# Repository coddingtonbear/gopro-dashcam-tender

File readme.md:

I use my GoPro as a dashcam, and although I rarely need to take any footage
off of my device, the GoPro will slowly accumulate videos over time.  This
device provides an easy way for me to clear the GoPro at the end of the 
day by just plugging my GoPro into it as its charger.

## Components Required

In order of decreasing expense:

* 1x ESP-12F: These can be obtained for roughly $2 on AliExpress.  Other similar packages of the ESP8266 wifi module, or _maybe_ even the ESP-01 module should work with minimal modifications to the layout and schematic.
* 1x CH340G: ~$0.50 on AliExpress.
* 1x SOT-223 3.3V Voltage Regulator
* 2x SOT-23 NPN Transistors for the UART->ESP8266 reset circuit.  Note that there are alternative reset circuits.  See below for details.
* 1x HC-49 12MHz crystal
* Miscellaneous passives.

See the schematic's netlist for more details.

## Procedure

Essentially, what this device does is:

* Wait for a GoPro to be plugged-in to the USB-A port.  This can be detected because of the way connected USB devices pull up the D+/D- lines to indicate their operating speed.
* Connect to my home WIFI network to get an up-to-date UTC time using NTP.  Immediately disconnecting from my home WIFI network.
* Connect to the GoPro WIFI network, then:
  * Set the GoPro's time.
  * Clear all stored media.
  * Turn off the GoPro.

## Schematic

## Errata

You'll notice two differences between the above schematic and the photo of the board above:

* I had originally intended to control the power supply to the attached GoPro using a mosfet (you'll see a jumper lead in the above photo between two of three leads nearby the USB-A connector.  It should've been clearer earlier, but I won't be able to detect the GoPro being plugged-in unless I'm supplying 5V; because the GoPro won't pull on the D+/D- lines until it is being supplied with voltage.
* I never populated the RGB LED in the bottom-left area of the board.  The footprint I've used in the above photo is essentially impossible to use on a milled board given the positioning of the pins on the SLV6A LED.  I've corrected the footprint in the attached project.
* You won't be able to tell in the above photo, but I had originally neglected to add a pulldown on GPIO15.  This caused the device to boot up into the wrong mode.  This bug took me a ton of time to find, and I only discovered what was wrong by connecting a logic analyzer to the ESP-12F's TX pin in autobaud mode to notice that the device was communicating its boot state after resetting.

## Future

* I'd probably not bother with the transitor-based reeset circuit.  The circuit in use here was copied from the NodeMCU schematic, and, although fairly simple, isn't really necessary given that PlatformIO's ESP8266 tooling supports using the DTR and RTS pins for directly controlling Reset and GPIO0 directly.

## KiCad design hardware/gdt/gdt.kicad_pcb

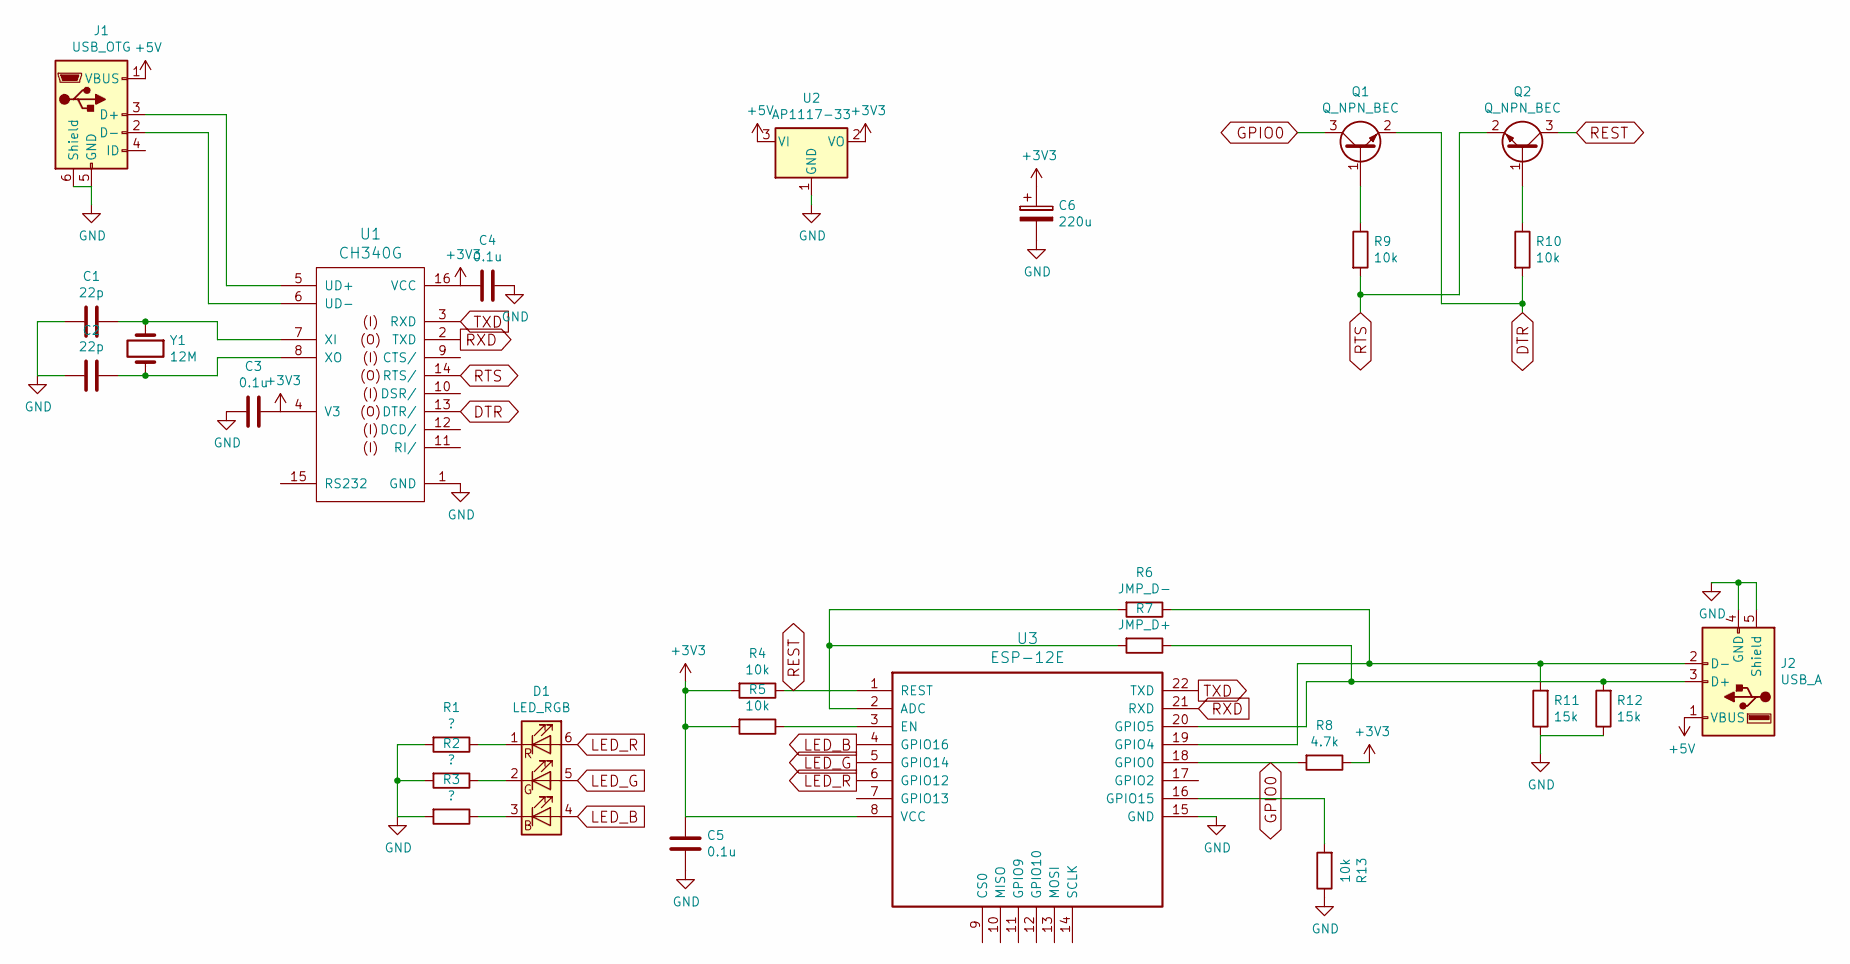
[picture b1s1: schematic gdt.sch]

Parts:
C1, C2: 22p; 0805_Milling
C3, C4, C5: 0.1u; 0805_Milling
C6: 220u; Capacitor_Electrolytic_D6.3xP2.5
D1: LED_RGB; SLV6A-FKB
J1: USB_OTG; UJ2-MIBH-4-SMT
J2: USB_A; USB_A_Female
Q1, Q2: Q_NPN_BEC; SOT-23_Handsoldering
R1, R2, R3: ?; 0805_Milling
R4, R5, R9, R10, R13: 10k; 0805_Milling
R6: JMP_D-; 0805_Milling
R7: JMP_D+; 0805_Milling
R8: 4.7k; 0805_Milling
R11, R12: 15k; 0805_Milling
U1: CH340G; SOIC-16
U2: AP1117-33; SOT223
U3: ESP-12E; ESP12E
Y1: 12M; XTAL-HC49US

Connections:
+3V3: C3.1, C4.2, C5.1, C6.1, R4.2, R5.2, R8.1, U1.4 (V3), U1.16 (VCC), U2.2 (VO), U3.8 (VCC)
+5V: J1.1 (VBUS), J2.1 (VBUS), U2.3 (VI)
DTR: Q1.2 (E), R10.2, U1.13 (DTR/)
GND: C1.2, C2.2, C3.2, C4.1, C5.2, C6.2, J1.5 (GND), J1.6 (Shield), J2.4 (GND), J2.5 (Shield), R1.2, R2.2, R3.2, R11.1, R12.1, R13.1, U1.1 (GND), U2.1 (GND), U3.15 (GND)
GPIO0: Q1.3 (C), R8.2, U3.18 (GPIO0)
LED_B: D1.4 (BA), U3.4 (GPIO16)
LED_G: D1.5 (GA), U3.5 (GPIO14)
LED_R: D1.6 (RA), U3.6 (GPIO12)
unnamed: C1.1, U1.7 (XI), Y1.1
unnamed: C2.1, U1.8 (XO), Y1.2
unnamed: D1.1 (RK), R1.1
unnamed: D1.2 (GK), R2.1
unnamed: D1.3 (BK), R3.1
unnamed: J1.2 (D-), U1.6 (UD-)
unnamed: J1.3 (D+), U1.5 (UD+)
unnamed: J2.2 (D-), R6.1, R11.2, U3.19 (GPIO4)
unnamed: J2.3 (D+), R7.1, R12.2, U3.20 (GPIO5)
unnamed: Q1.1 (B), R9.1
unnamed: Q2.1 (B), R10.1
unnamed: R5.1, U3.3 (EN)
unnamed: R6.2, R7.2, U3.2 (ADC)
unnamed: R13.2, U3.16 (GPIO15)
REST: Q2.3 (C), R4.1, U3.1 (REST)
RTS: Q2.2 (E), R9.2, U1.14 (RTS/)
RXD: U1.2 (TXD), U3.21 (RXD)
TXD: U1.3 (RXD), U3.22 (TXD)

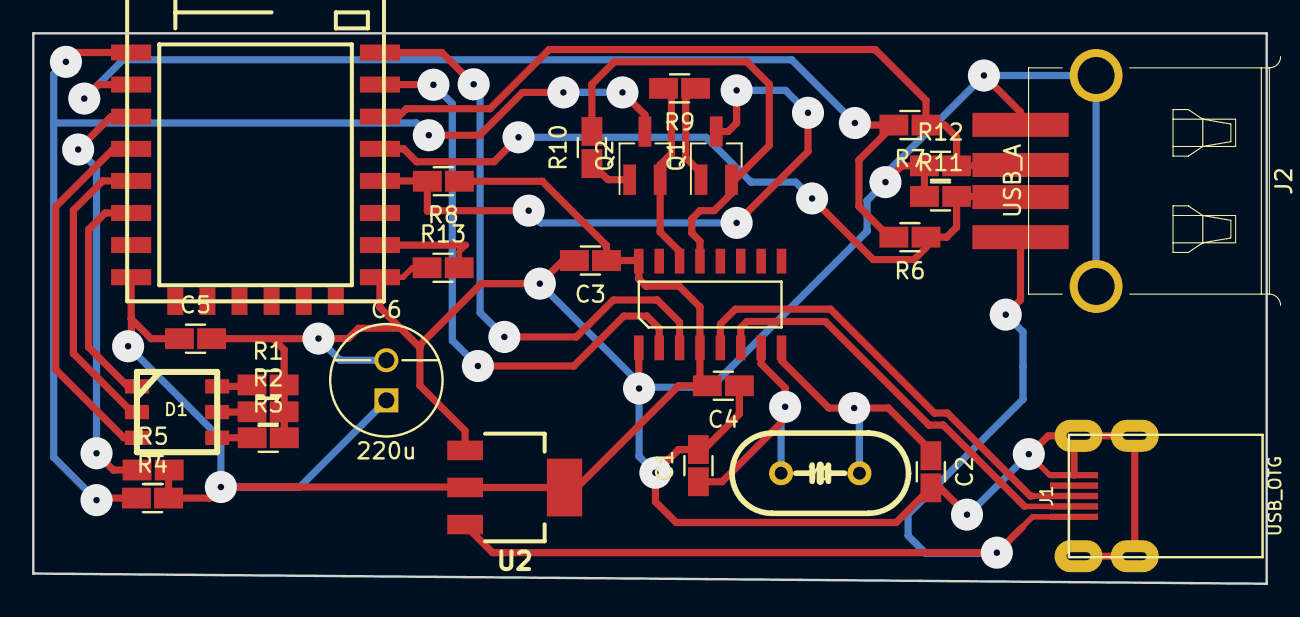
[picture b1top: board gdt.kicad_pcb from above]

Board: 2 copper layers, 76.8 x 34.3 mm, 28 parts (0 on the bottom side), 26 nets.

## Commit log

2017-10-17 And so it begins...
2017-10-20 Whoops; this put it into boot mode 5 during reset rather than 1 -- forgot a pulldown resistor.
2017-10-26 Uploading final version of hardware/software.
2017-10-26 Update readme.md
    Updating readme to include a brief overview of the project. Now I can call this project complete (enough).
2017-10-26 Update readme.md
    Whoops; those aren't mosfets.
